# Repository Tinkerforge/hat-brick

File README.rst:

HAT Brick
=========

This repository contains the firmware source code and the hardware design
files. The documentation generator configs can be found at
https://github.com/Tinkerforge/generators

Repository Content
------------------

software/:
 * examples/: Examples for all supported languages
 * build/: Compiled files
 * src/: Source code of firmware
 * Makefile: Makefile to build project

hardware/:
 * Contains KiCad project files and additionally schematics as PDF

datasheets/:
 * Contains datasheets for sensors and complex ICs that are used

Hardware
--------

The hardware is designed with the open source EDA Suite KiCad
(http://www.kicad.org). Before you are able to open the files,
you have to install the Tinkerforge kicad-libraries
(https://github.com/Tinkerforge/kicad-libraries). You can either clone
them directly in hardware/ or clone them in a separate folder and
symlink them into hardware/
(ln -s kicad_path/kicad-libraries project_path/hardware). After that you
can open the .pro file in hardware/ with KiCad and from there view and
modify the schematics and the PCB layout.

Software
--------

If you want to do your own Brick/Bricklet firmware development we highly
recommend that you use our build environment setup script and read the
tutorial (https://www.tinkerforge.com/en/doc/Tutorials/Tutorial_Build_Environment/Tutorial.html).

To compile the C code we recommend you to install the newest GNU Arm Embedded
Toolchain (https://launchpad.net/gcc-arm-embedded/+download).
You also need to install bricklib2 (https://github.com/Tinkerforge/bricklib2).

You can either clone it directly in software/src/ or clone it in a
separate folder and symlink it into software/src/
(ln -s bricklib_path/bricklib2 project_path/software/src/). Finally make sure to
have CMake installed (http://www.cmake.org/cmake/resources/software.html).

After that you can build the firmware by invoking make in software/.
The firmware (.zbin) can then be found in software/build/ and uploaded
with brickv (click button "Flashing" on start screen).

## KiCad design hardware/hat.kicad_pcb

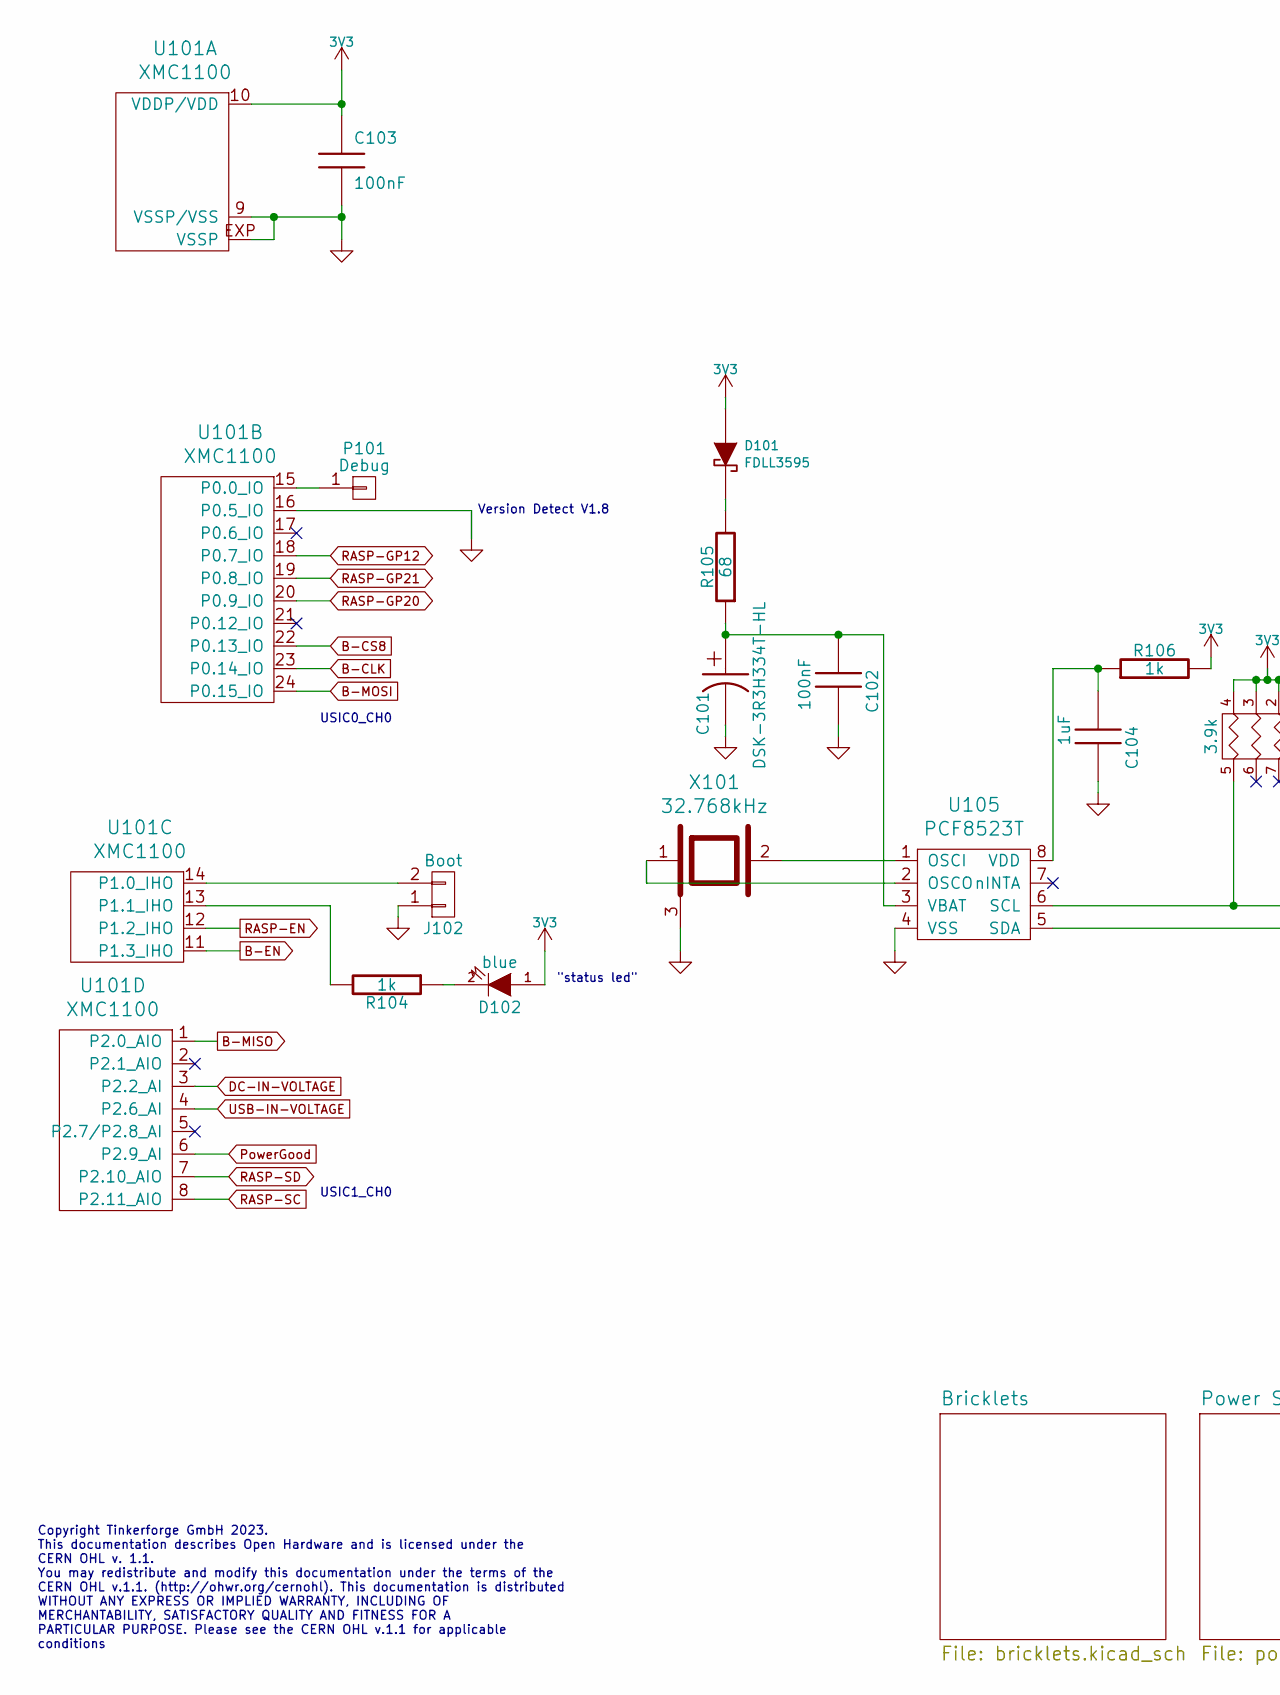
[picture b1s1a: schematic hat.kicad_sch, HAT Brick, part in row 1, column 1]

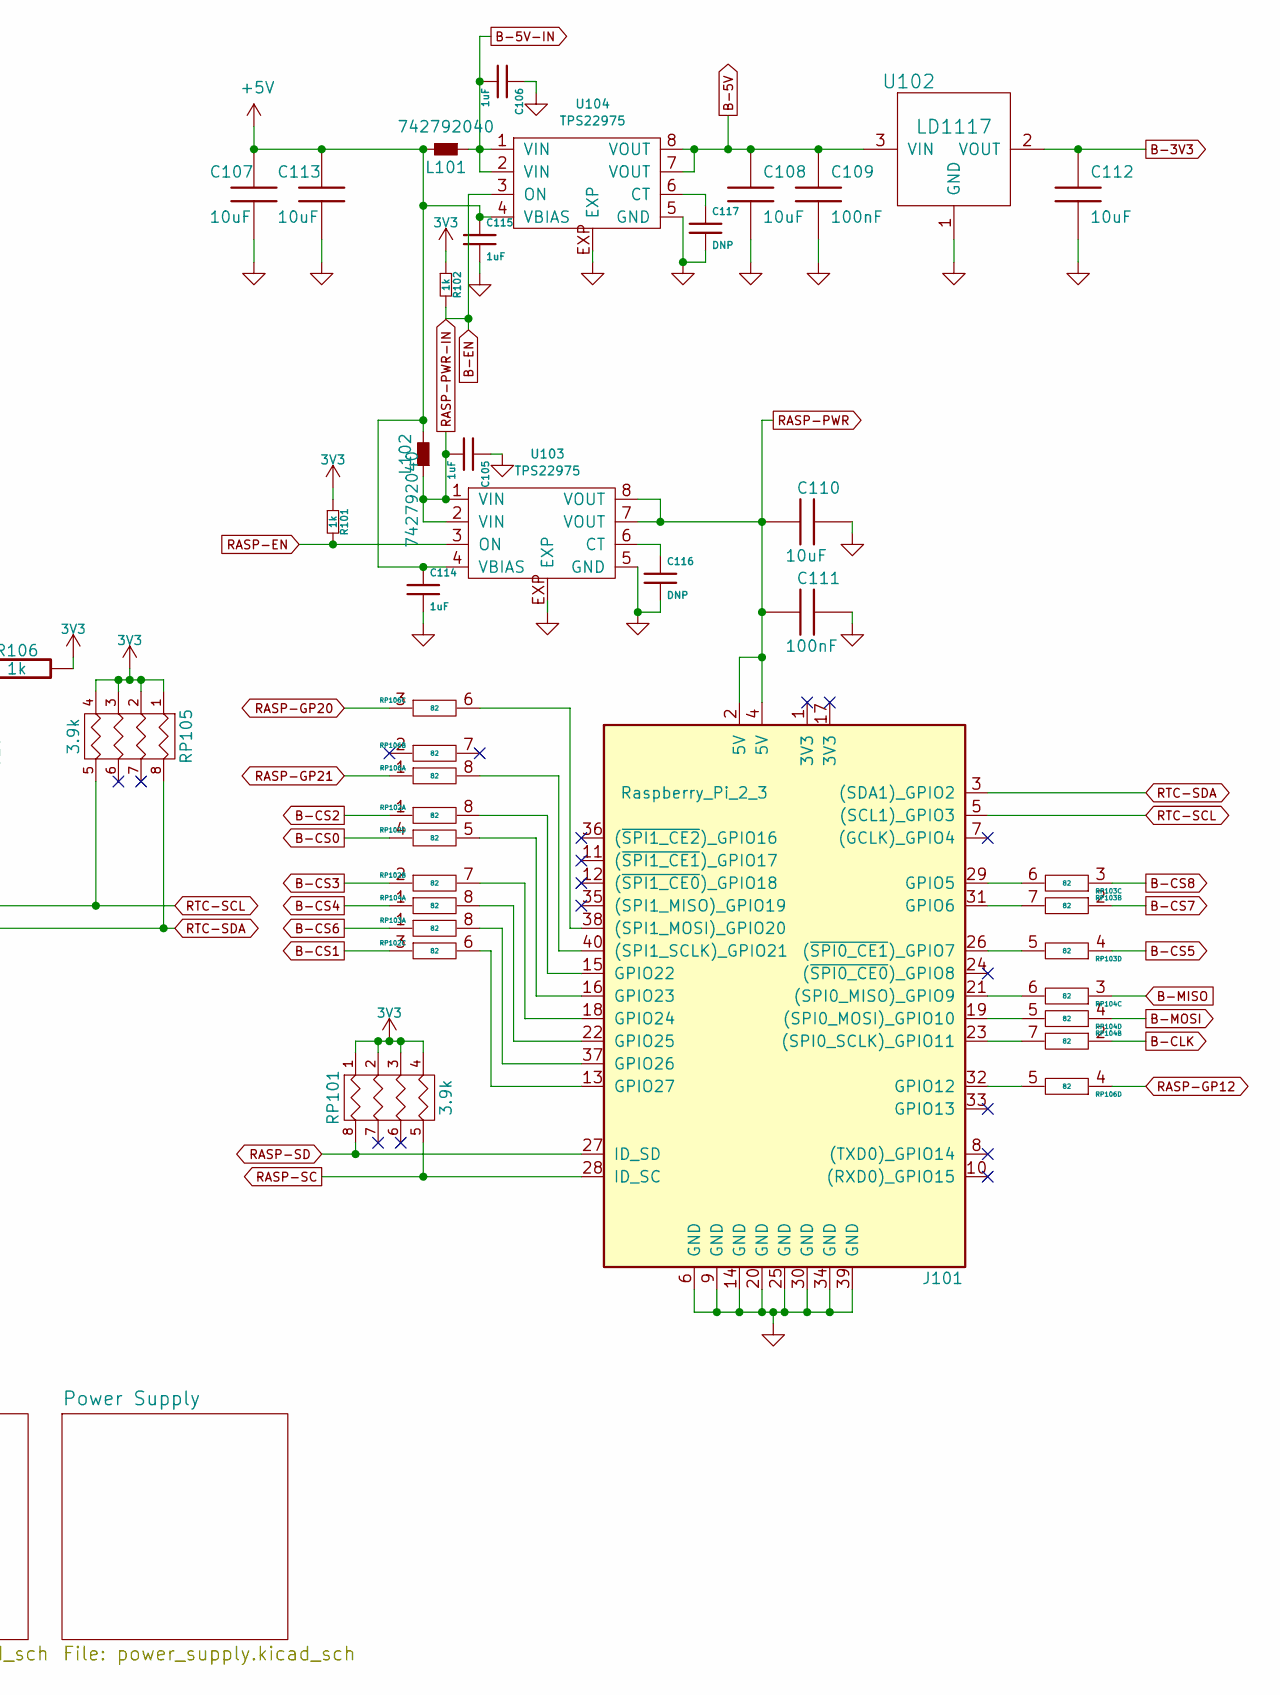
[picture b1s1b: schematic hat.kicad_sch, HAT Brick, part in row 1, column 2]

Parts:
C101: DSK-3R3H334T-HL; DSK
C102, C103, C109, C111: 100nF; C0603F
C104, C105, C106, C114, C115: 1uF; C0603F
C107, C108, C110, C112, C113: 10uF; C1206
C116, C117: DNP; C0402F
D101: FDLL3595; MiniMelf
D102: blue; D0603F
J101: Raspberry_Pi_2_3; raspberrypi_hat2
J102: Boot; SolderJumper
L101, L102: 742792040; R0805
P101: Debug; DEBUG_PAD
R101, R102, R104, R106: 1k; R0603F
R105: 68; R0603F
RP101, RP105: 3.9k; 4X0402
RP102, RP103, RP104, RP106: 82; 4X0402
U101: XMC1100; QFN24-4x4mm-0.5mm
U102: LD1117; SOT-223
U103, U104: TPS22975; WSON8-2x2
U105: PCF8523T; SO-8
X101: 32.768kHz; AB26TRQ

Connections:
3V3: C103.1, D101.1 (A), D102.1 (A), R101.1, R102.1, R106.2, RP101.1, RP101.2, RP101.3, RP101.4, RP105.1, RP105.2, RP105.3, RP105.4, U101.10 (VDDP/VDD); also elsewhere on the board
+5V: C107.1, C113.1, C114.1, C115.1, L101.2, L102.2, U103.4 (VBIAS), U104.4 (VBIAS); also elsewhere on the board
B-3V3: C112.1, U102.2 (VOUT); also elsewhere on the board
B-5V: C108.1, C109.1, U102.3 (VIN), U104.7 (VOUT), U104.8 (VOUT); also elsewhere on the board
B-5V-IN: C106.2, L101.1, U104.1 (VIN), U104.2 (VIN)
B-CLK: RP104.2, U101.23 (P0.14_IO); also elsewhere on the board
B-CS0: RP102.4; also elsewhere on the board
B-CS1: RP102.3; also elsewhere on the board
B-CS2: RP102.1; also elsewhere on the board
B-CS3: RP102.2; also elsewhere on the board
B-CS4: RP104.1; also elsewhere on the board
B-CS5: RP103.4; also elsewhere on the board
B-CS6: RP103.1; also elsewhere on the board
B-CS7: RP103.2; also elsewhere on the board
B-CS8: RP103.3, U101.22 (P0.13_IO)
B-EN: R102.2, U101.11 (P1.3_IHO), U104.3 (ON)
B-MISO: RP104.3, U101.1 (P2.0_AIO); also elsewhere on the board
B-MOSI: RP104.4, U101.24 (P0.15_IO); also elsewhere on the board
DC-IN-VOLTAGE: U101.3 (P2.2_AI); also elsewhere on the board
GND: C101.2, C102.1, C103.2, C104.1, C105.1, C106.1, C107.2, C108.2, C109.2, C110.1, C111.1, C112.2, C113.2, C114.2, C115.2, C116.2, C117.2, J101.6 (GND), J101.9 (GND), J101.14 (GND), J101.20 (GND), J101.25 (GND), J101.30 (GND), J101.34 (GND), J101.39 (GND), J102.1, U101.9 (VSSP/VSS), U101.16 (P0.5_IO), U101.EXP (VSSP), U102.1 (GND), U103.5 (GND), U103.EXP, U104.5 (GND), U104.EXP, U105.4 (VSS), X101.3; also elsewhere on the board
unnamed: C101.1, C102.2, R105.1, U105.3 (VBAT)
unnamed: C104.2, R106.1, U105.8 (VDD)
unnamed: C116.1, U103.6 (CT)
unnamed: C117.1, U104.6 (CT)
unnamed: D101.2 (K), R105.2
unnamed: D102.2 (K), R104.1
unnamed: J101.13 (GPIO27), RP102.6
unnamed: J101.15 (GPIO22), RP102.8
unnamed: J101.16 (GPIO23), RP102.5
unnamed: J101.18 (GPIO24), RP102.7
unnamed: J101.19 ((SPI0_MOSI)_GPIO10), RP104.5
unnamed: J101.21 ((SPI0_MISO)_GPIO9), RP104.6
unnamed: J101.22 (GPIO25), RP104.8
unnamed: J101.23 ((SPI0_SCLK)_GPIO11), RP104.7
unnamed: J101.26 ((~SPI0_CE1)_GPIO7), RP103.5
unnamed: J101.29 (GPIO5), RP103.6
unnamed: J101.31 (GPIO6), RP103.7
unnamed 62: J101.32 (GPIO12), RP106.5; also elsewhere on the board
unnamed: J101.37 (GPIO26), RP103.8
unnamed: J102.2, U101.14 (P1.0_IHO)
unnamed: P101.1, U101.15 (P0.0_IO)
unnamed: R104.2, U101.13 (P1.1_IHO)
unnamed: RP106.1, U101.19 (P0.8_IO)
unnamed: RP106.3, U101.20 (P0.9_IO)
unnamed: J101.38 ((SPI1_MOSI)_GPIO20), RP106.6
unnamed: J101.40 ((SPI1_SCLK)_GPIO21), RP106.8
unnamed: U105.1 (OSCI), X101.2
unnamed: U105.2 (OSCO), X101.1
PowerGood: U101.6 (P2.9_AI); also elsewhere on the board
RASP-EN: R101.2, U101.12 (P1.2_IHO), U103.3 (ON)
RASP-GP: RP106.4, U101.18 (P0.7_IO); also elsewhere on the board
RASP-PWR: C110.2, C111.2, J101.2 (5V), J101.4 (5V), U103.7 (VOUT), U103.8 (VOUT)
RASP-PWR-IN: C105.2, L102.1, U103.1 (VIN), U103.2 (VIN)
RASP-SC: J101.28 (ID_SC), RP101.5 (R4), U101.8 (P2.11_AIO)
RASP-SD: J101.27 (ID_SD), RP101.8 (R1), U101.7 (P2.10_AIO)
RTC-SCL: J101.5 ((SCL1)_GPIO3), RP105.5 (R4), U105.6 (SCL)
RTC-SDA: J101.3 ((SDA1)_GPIO2), RP105.8 (R1), U105.5 (SDA)
USB-IN-VOLTAGE: U101.4 (P2.6_AI); also elsewhere on the board

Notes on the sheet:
"status led"
USIC1_CH0
Version Detect V1.8
Copyright Tinkerforge GmbH 2023. This documentation describes Open Hardware and is licensed under the CERN OHL v. 1.1. You may redistribute and modify this documentation under the terms of the CERN OHL v.1.1. (http://ohwr.org/cernohl). This documentation is distributed WITHOUT ANY EXPRESS OR IMPLIE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
USIC0_CH0

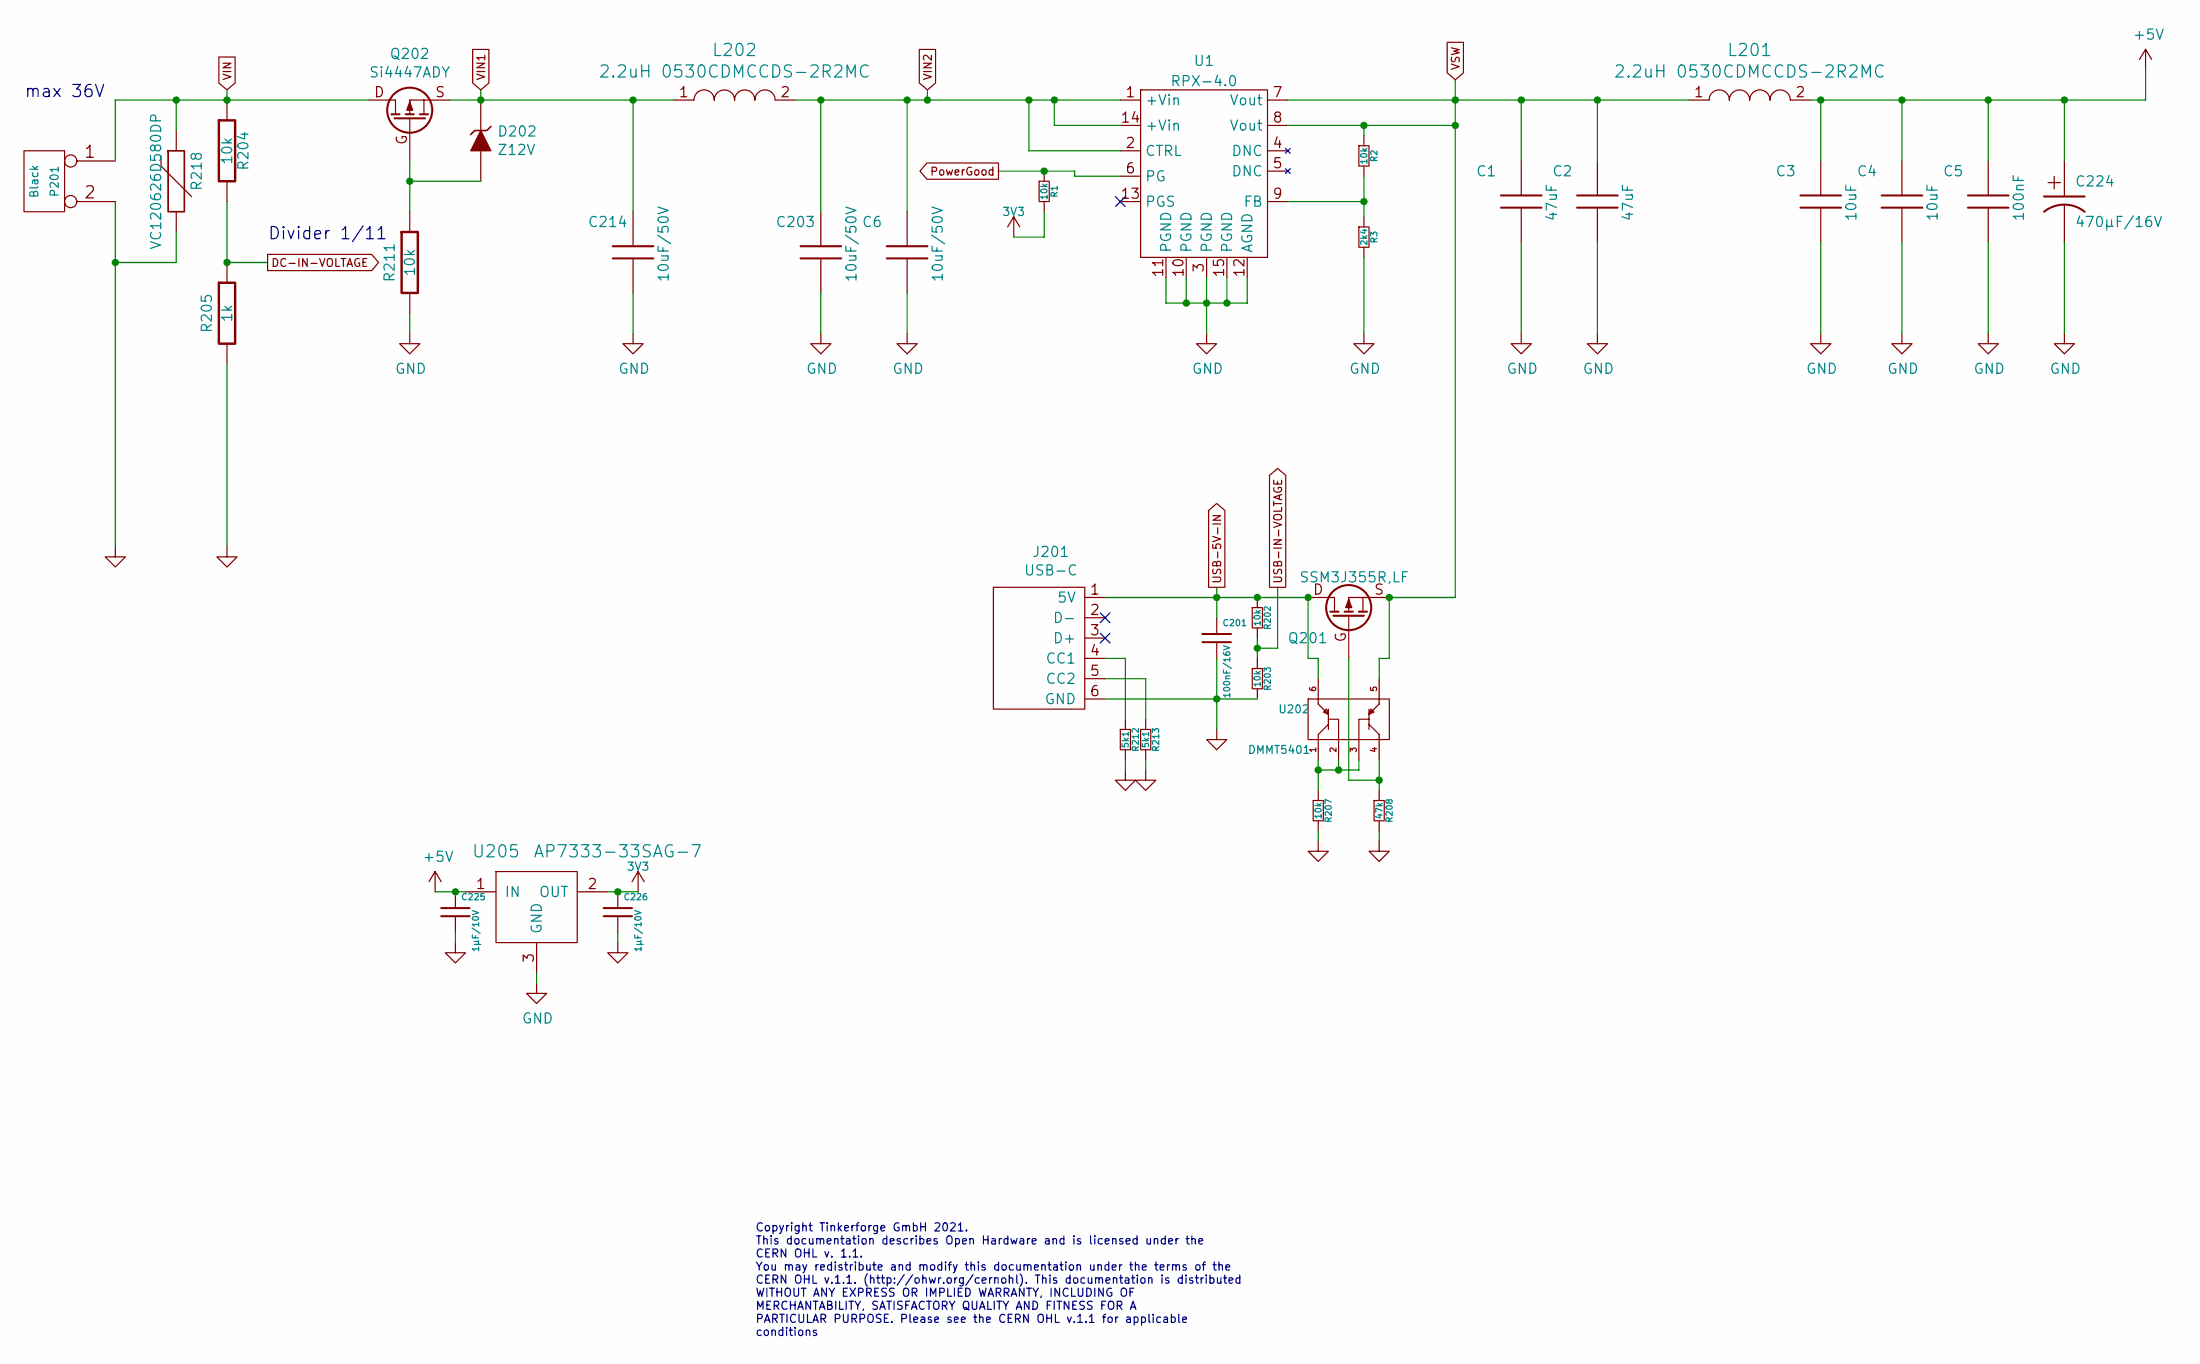
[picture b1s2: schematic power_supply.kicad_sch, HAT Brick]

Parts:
C1, C2: 47uF; C1210
C3, C4: 10uF; C0805E
C5: 100nF; C0603F
C6, C203, C214: 10uF/50V; C1210
C201: 100nF/16V; C0603F
C224: 470µF/16V; ELKO_83
C225, C226: 1µF/10V; C0603F
D202: Z12V; SOD-123
J201: USB-C
L201, L202: 2.2uH 0530CDMCCDS-2R2MC; NRS5030
P201: Black; OQ_2P
Q201: SSM3J355R,LF; SOT23GDS
Q202: Si4447ADY; SOIC-8-MOSFET
R1, R2, R202, R203, R204, R207, R211: 10k; R0603F
R3: 2k4; R0603F
R205: 1k; R0603F
R208: 47k; R0603F
R212, R213: 5k1; R0603F
R218: VC120626D580DP; R1206
U1: RPX-4.0
U202: DMMT5401; SOT26
U205: AP7333-33SAG-7; SOT23-3

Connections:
3V3: C226.1, R1.2, U205.2 (OUT); also elsewhere on the board
+5V: C3.1, C4.1, C5.1, C224.1, C225.1, L201.2, U205.1 (IN); also elsewhere on the board
DC-IN-VOLTAGE: R204.2, R205.1; also elsewhere on the board
GND: C1.2, C2.2, C3.2, C4.2, C5.2, C6.2, C201.2, C203.2, C214.2, C224.2, C225.2, C226.2, J201.6 (GND), P201.2 (PM), R3.2, R203.2, R205.2, R207.2, R208.2, R211.2, R212.2, R213.2, R218.2, U1.3 (PGND), U1.10 (PGND), U1.11 (PGND), U1.12 (AGND), U1.15 (PGND), U205.3 (GND); also elsewhere on the board
unnamed: D202.1 (A), Q202.G, R211.1
unnamed: J201.4 (CC1), R212.1
unnamed: J201.5 (CC2), R213.1
unnamed: Q201.G, R208.1, U202.4
unnamed: R2.2, R3.1, U1.9 (FB)
unnamed: R207.1, U202.1, U202.2, U202.3
PowerGood: R1.1, U1.6 (PG); also elsewhere on the board
USB-5V-IN: C201.1, J201.1 (5V), Q201.D, R202.1, U202.6
USB-IN-VOLTAGE: R202.2, R203.1; also elsewhere on the board
VIN: P201.1, Q202.D, R204.1, R218.1
VIN1: C214.1, D202.2 (K), L202.1, Q202.S
VIN2: C6.1, C203.1, L202.2, U1.1 (+Vin), U1.2 (CTRL), U1.14 (+Vin)
VSW: C1.1, C2.1, L201.1, Q201.S, R2.1, U1.7 (Vout), U1.8 (Vout), U202.5

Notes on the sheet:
Divider 1/11
Copyright Tinkerforge GmbH 2021. This documentation describes Open Hardware and is licensed under the CERN OHL v. 1.1. You may redistribute and modify this documentation under the terms of the CERN OHL v.1.1. (http://ohwr.org/cernohl). This documentation is distributed WITHOUT ANY EXPRESS OR IMPLIE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
max 36V

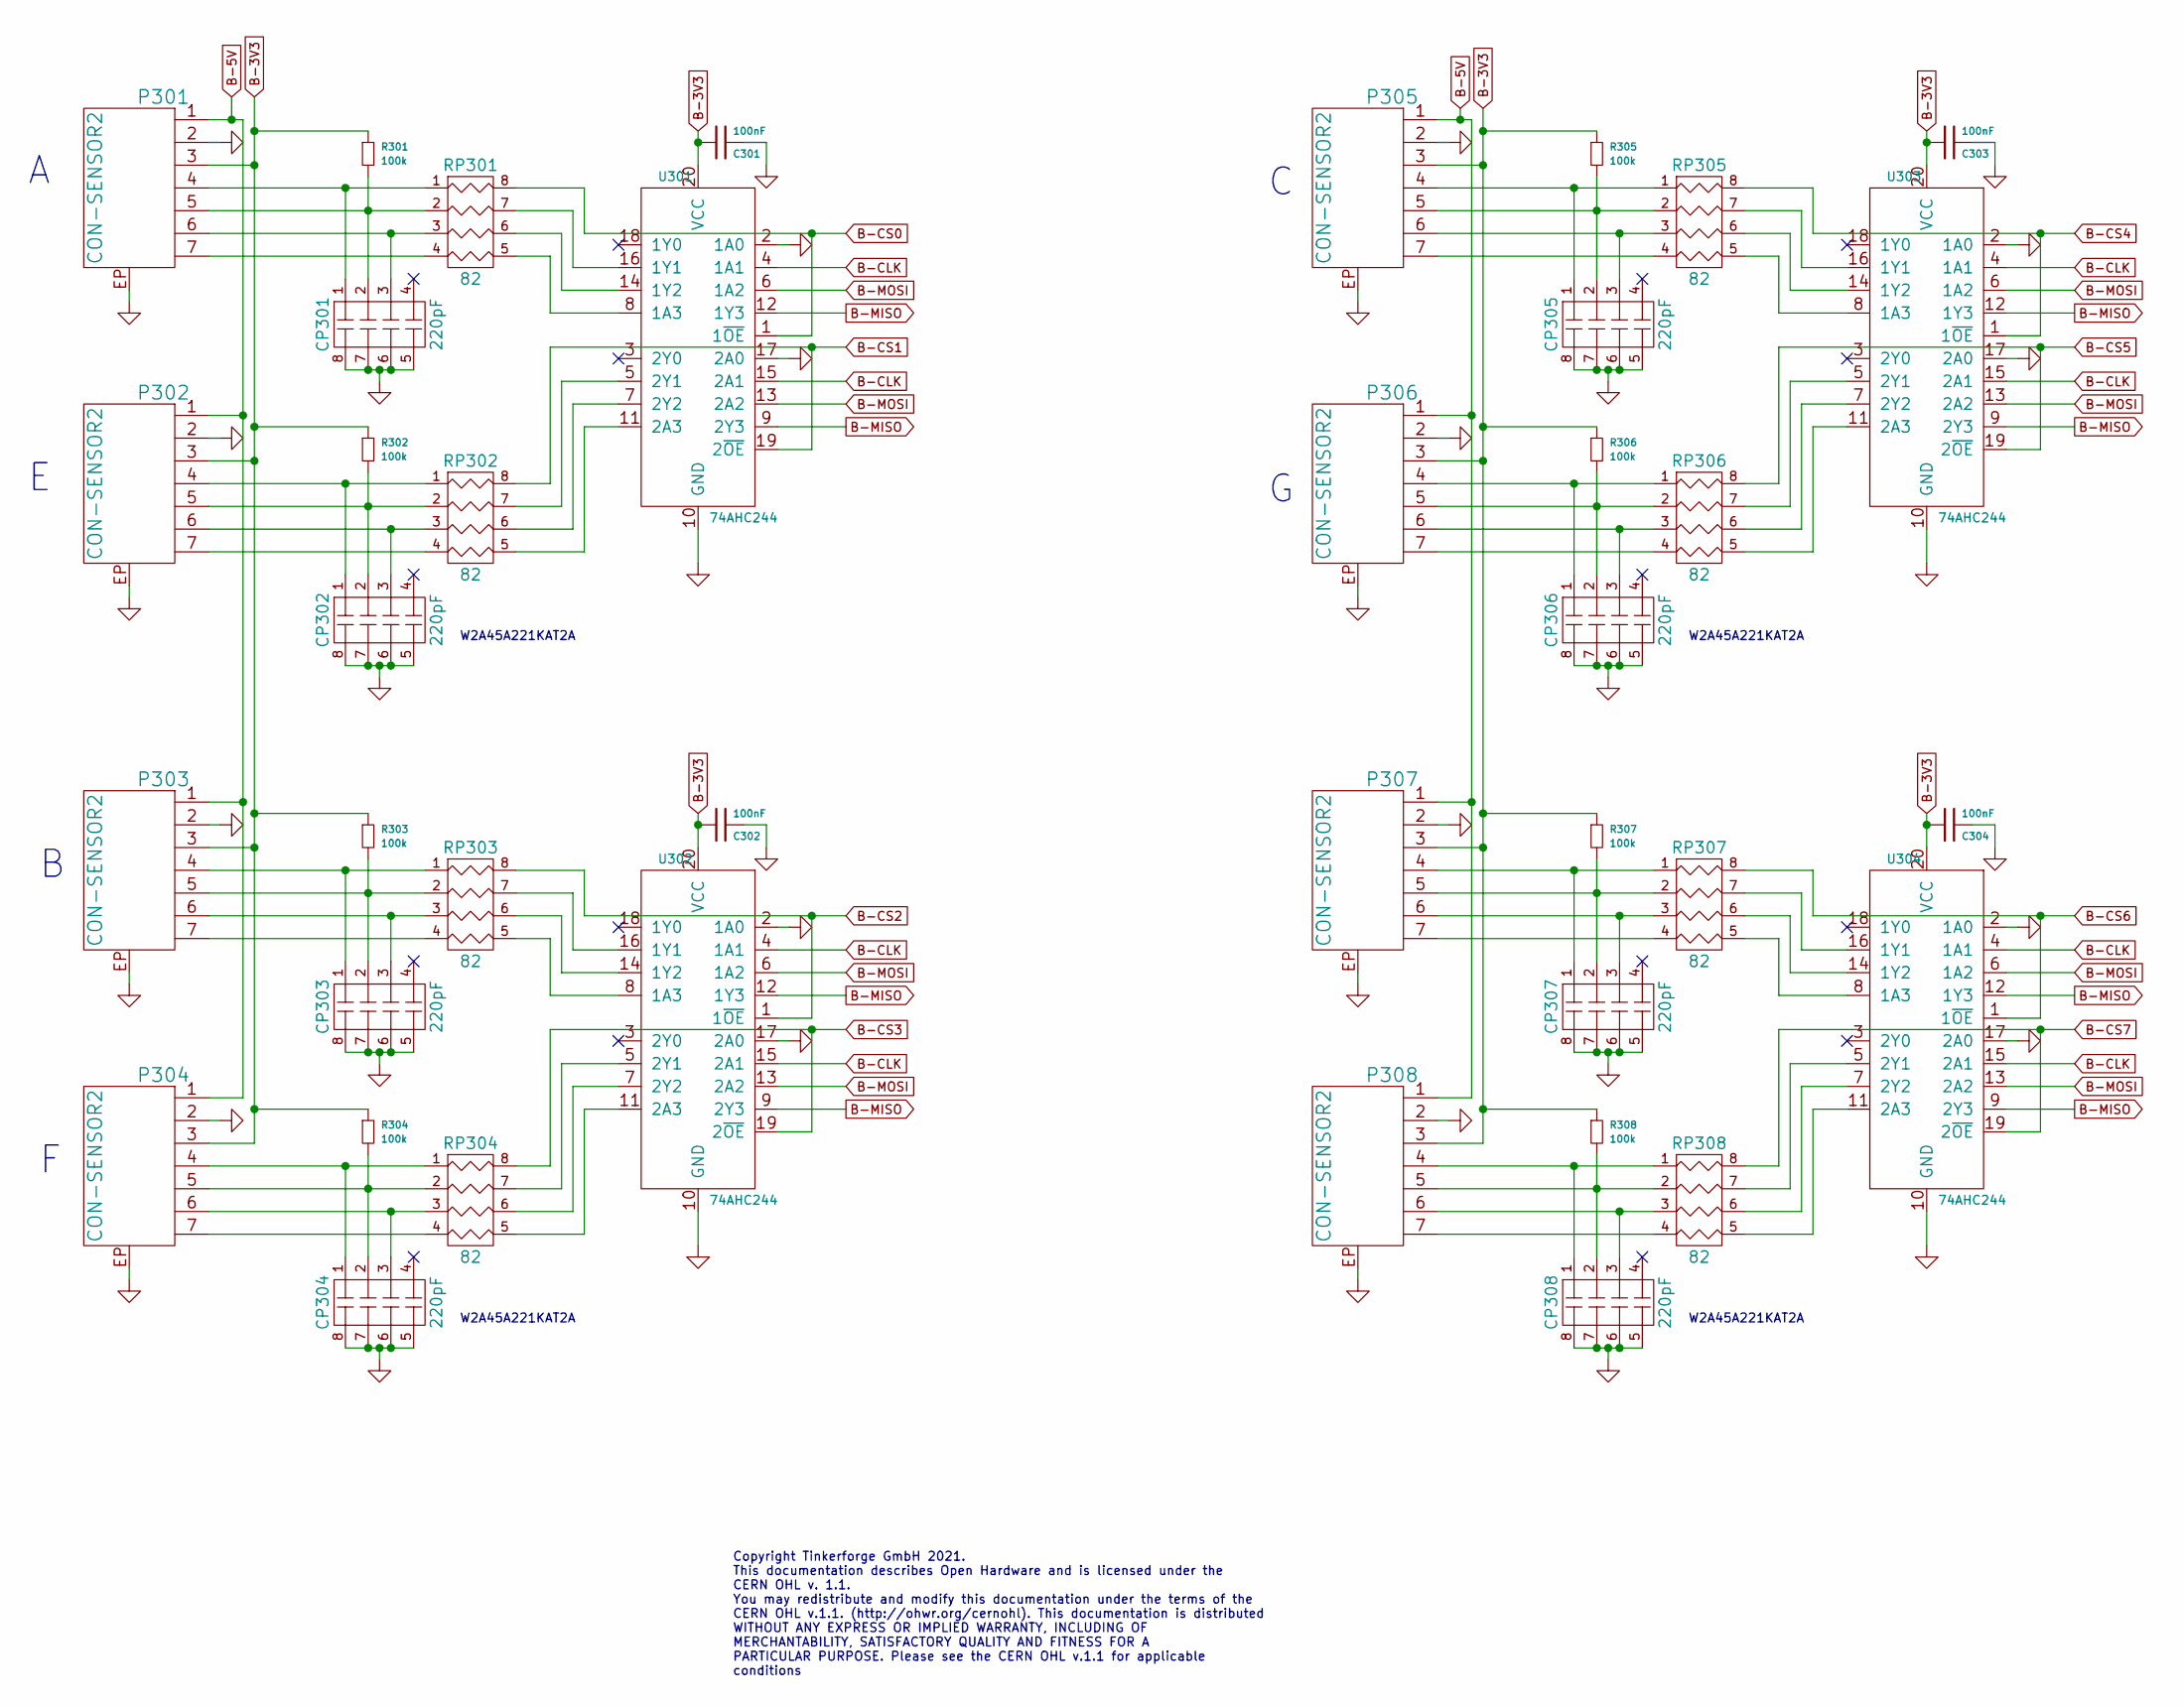
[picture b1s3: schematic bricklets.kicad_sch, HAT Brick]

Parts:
C301, C302, C303, C304: 100nF; C0603F
CP301, CP302, CP303, CP304, CP305, CP306, CP307, CP308: 220pF; 4X0402
P301, P302, P303, P304, P305, P306, P307, P308: CON-SENSOR2; CON-SENSOR2_180
R301, R302, R303, R304, R305, R306, R307, R308: 100k; R0402F
RP301, RP302, RP303, RP304, RP305, RP306, RP307, RP308: 82; 4X0402
U301, U302, U303, U304: 74AHC244; TSSOP20

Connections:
B-3V3: C301.2, C302.2, C303.2, C304.2, P301.3, P302.3, P303.3, P304.3, P305.3, P306.3, P307.3, P308.3, R301.1, R302.1, R303.1, R304.1, R305.1, R306.1, R307.1, R308.1, U301.20 (VCC), U302.20 (VCC), U303.20 (VCC), U304.20 (VCC); also elsewhere on the board
B-5V: P301.1, P302.1, P303.1, P304.1, P305.1, P306.1, P307.1, P308.1; also elsewhere on the board
B-CLK: U301.4 (1A1), U301.15 (2A1), U302.4 (1A1), U302.15 (2A1), U303.4 (1A1), U303.15 (2A1), U304.4 (1A1), U304.15 (2A1); also elsewhere on the board
B-CS0: RP301.8 (R1), U301.1 (1~OE); also elsewhere on the board
B-CS1: RP302.8 (R1), U301.19 (2~OE); also elsewhere on the board
B-CS2: RP303.8 (R1), U302.1 (1~OE); also elsewhere on the board
B-CS3: RP304.8 (R1), U302.19 (2~OE); also elsewhere on the board
B-CS4: RP305.8 (R1), U303.1 (1~OE); also elsewhere on the board
B-CS5: RP306.8 (R1), U303.19 (2~OE); also elsewhere on the board
B-CS6: RP307.8 (R1), U304.1 (1~OE); also elsewhere on the board
B-CS7: RP308.8 (R1), U304.19 (2~OE); also elsewhere on the board
B-MISO: U301.9 (2Y3), U301.12 (1Y3), U302.9 (2Y3), U302.12 (1Y3), U303.9 (2Y3), U303.12 (1Y3), U304.9 (2Y3), U304.12 (1Y3); also elsewhere on the board
B-MOSI: U301.6 (1A2), U301.13 (2A2), U302.6 (1A2), U302.13 (2A2), U303.6 (1A2), U303.13 (2A2), U304.6 (1A2), U304.13 (2A2); also elsewhere on the board
GND: C301.1, C302.1, C303.1, C304.1, CP301.5 (R4), CP301.6 (R3), CP301.7 (R2), CP301.8 (R1), CP302.5 (R4), CP302.6 (R3), CP302.7 (R2), CP302.8 (R1), CP303.5 (R4), CP303.6 (R3), CP303.7 (R2), CP303.8 (R1), CP304.5 (R4), CP304.6 (R3), CP304.7 (R2), CP304.8 (R1), CP305.5 (R4), CP305.6 (R3), CP305.7 (R2), CP305.8 (R1), CP306.5 (R4), CP306.6 (R3), CP306.7 (R2), CP306.8 (R1), CP307.5 (R4), CP307.6 (R3), CP307.7 (R2), CP307.8 (R1), CP308.5 (R4), CP308.6 (R3), CP308.7 (R2), CP308.8 (R1), P301.2, P301.EP, P302.2, P302.EP, P303.2, P303.EP, P304.2, P304.EP, P305.2, P305.EP, P306.2, P306.EP, P307.2, P307.EP, P308.2, P308.EP, U301.2 (1A0), U301.10 (GND), U301.17 (2A0), U302.2 (1A0), U302.10 (GND), U302.17 (2A0), U303.2 (1A0), U303.10 (GND), U303.17 (2A0), U304.2 (1A0), U304.10 (GND), U304.17 (2A0); also elsewhere on the board
unnamed: CP301.1, P301.4, RP301.1
unnamed: CP301.2, P301.5, R301.2, RP301.2
unnamed: CP301.3, P301.6, RP301.3
unnamed: CP302.1, P302.4, RP302.1
unnamed: CP302.2, P302.5, R302.2, RP302.2
unnamed: CP302.3, P302.6, RP302.3
unnamed: CP303.1, P303.4, RP303.1
unnamed: CP303.2, P303.5, R303.2, RP303.2
unnamed: CP303.3, P303.6, RP303.3
unnamed: CP304.1, P304.4, RP304.1
unnamed: CP304.2, P304.5, R304.2, RP304.2
unnamed: CP304.3, P304.6, RP304.3
unnamed: CP305.1, P305.4, RP305.1
unnamed: CP305.2, P305.5, R305.2, RP305.2
unnamed: CP305.3, P305.6, RP305.3
unnamed: CP306.1, P306.4, RP306.1
unnamed: CP306.2, P306.5, R306.2, RP306.2
unnamed: CP306.3, P306.6, RP306.3
unnamed: CP307.1, P307.4, RP307.1
unnamed: CP307.2, P307.5, R307.2, RP307.2
unnamed: CP307.3, P307.6, RP307.3
unnamed: CP308.1, P308.4, RP308.1
unnamed: CP308.2, P308.5, R308.2, RP308.2
unnamed: CP308.3, P308.6, RP308.3
unnamed: P301.7, RP301.4
unnamed: P302.7, RP302.4
unnamed: P303.7, RP303.4
unnamed: P304.7, RP304.4
unnamed: P305.7, RP305.4
unnamed: P306.7, RP306.4
unnamed: P307.7, RP307.4
unnamed: P308.7, RP308.4
unnamed: RP301.5 (R4), U301.8 (1A3)
unnamed: RP301.6 (R3), U301.14 (1Y2)
unnamed: RP301.7 (R2), U301.16 (1Y1)
unnamed: RP302.5 (R4), U301.11 (2A3)
unnamed: RP302.6 (R3), U301.7 (2Y2)
unnamed: RP302.7 (R2), U301.5 (2Y1)
unnamed: RP303.5 (R4), U302.8 (1A3)
unnamed: RP303.6 (R3), U302.14 (1Y2)
unnamed: RP303.7 (R2), U302.16 (1Y1)
unnamed: RP304.5 (R4), U302.11 (2A3)
unnamed: RP304.6 (R3), U302.7 (2Y2)
unnamed: RP304.7 (R2), U302.5 (2Y1)
unnamed: RP305.5 (R4), U303.8 (1A3)
unnamed: RP305.6 (R3), U303.14 (1Y2)
unnamed: RP305.7 (R2), U303.16 (1Y1)
unnamed: RP306.5 (R4), U303.11 (2A3)
unnamed: RP306.6 (R3), U303.7 (2Y2)
unnamed: RP306.7 (R2), U303.5 (2Y1)
unnamed: RP307.5 (R4), U304.8 (1A3)
unnamed: RP307.6 (R3), U304.14 (1Y2)
unnamed: RP307.7 (R2), U304.16 (1Y1)
unnamed: RP308.5 (R4), U304.11 (2A3)
unnamed: RP308.6 (R3), U304.7 (2Y2)
unnamed: RP308.7 (R2), U304.5 (2Y1)

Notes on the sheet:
W2A45A221KAT2A
Copyright Tinkerforge GmbH 2021. This documentation describes Open Hardware and is licensed under the CERN OHL v. 1.1. You may redistribute and modify this documentation under the terms of the CERN OHL v.1.1. (http://ohwr.org/cernohl). This documentation is distributed WITHOUT ANY EXPRESS OR IMPLIE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

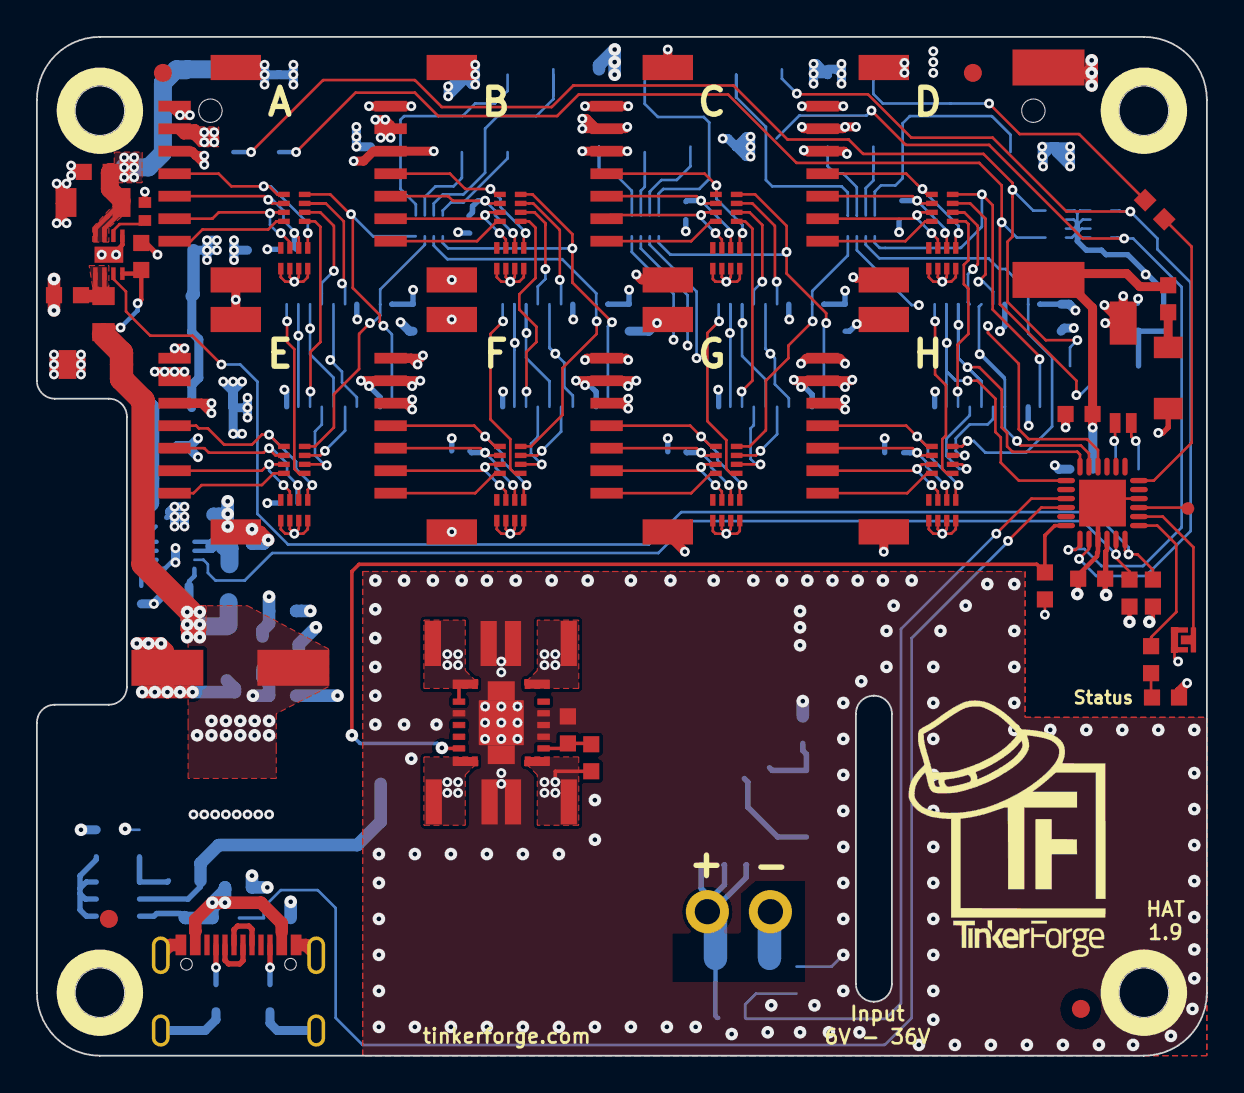
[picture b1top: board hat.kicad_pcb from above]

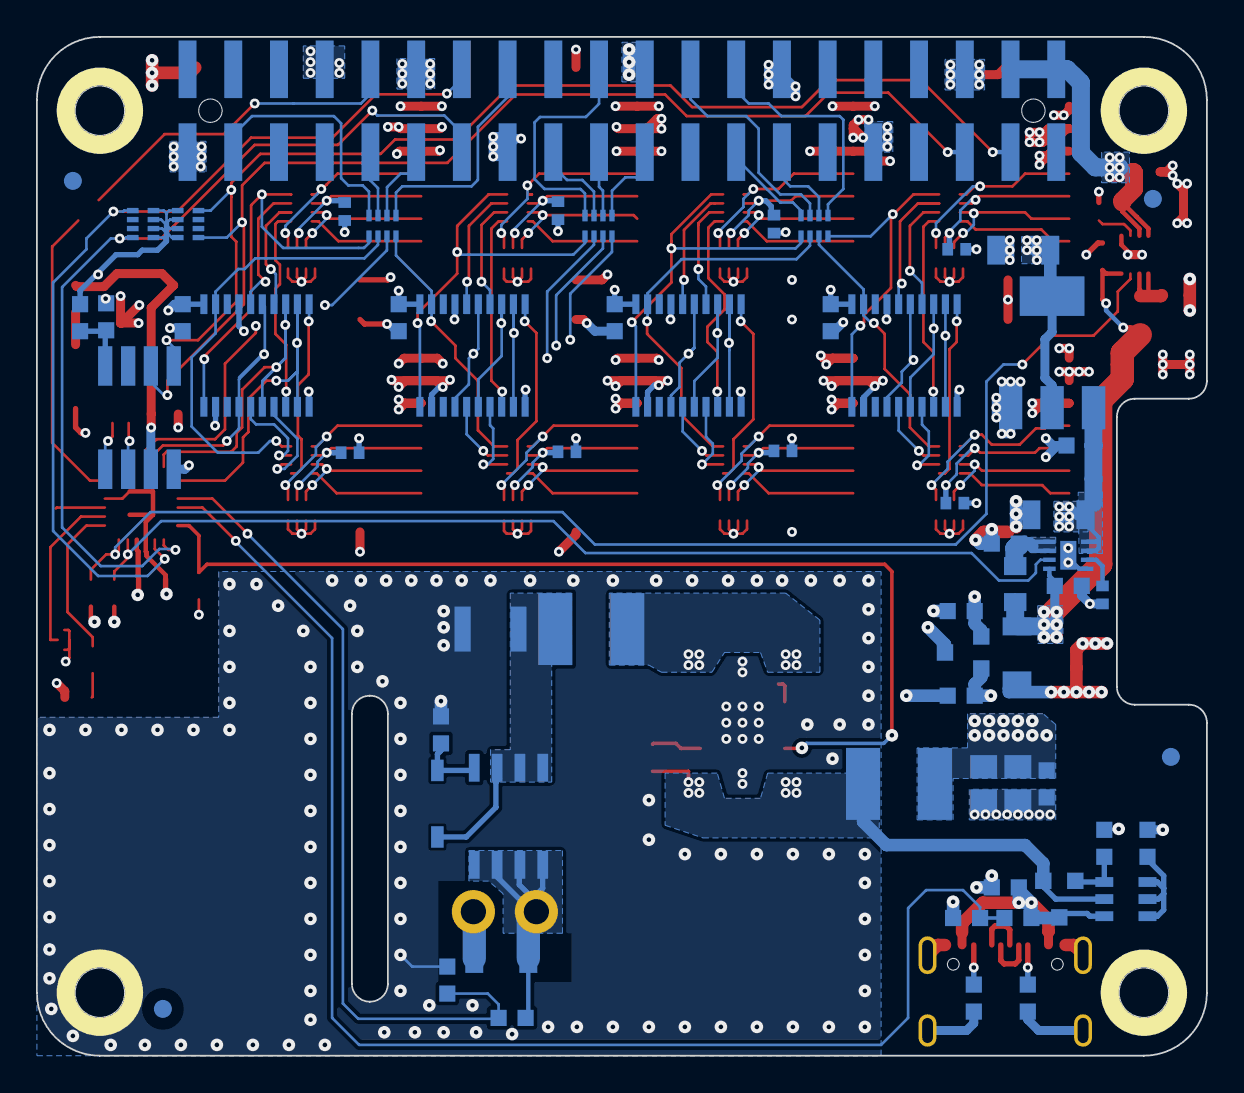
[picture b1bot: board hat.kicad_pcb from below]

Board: 4 copper layers, 65.0 x 56.6 mm, 124 parts (63 on the bottom side), 121 nets.

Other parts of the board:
Fiducial_Mark: VAL**; Fiducial_Mark
Fiducial_Mark#2, Fiducial_Mark#3, Fiducial_Mark#4, Fiducial_Mark#5, Fiducial_Mark#6, Fiducial_Mark#7, Fiducial_Mark#8: VAL**; Fiducial_Mark
R103: 1k; R0603F

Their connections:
unnamed 62: R103.2; also elsewhere on the board
RASP-GP: R103.1; also elsewhere on the board

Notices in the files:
hardware/bricklets.kicad_sch:
Licensed under CERN OHL v.1.1
Copyright (©) 2023, T.Schneidermann
